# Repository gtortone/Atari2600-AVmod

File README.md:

# Atari2600-AVmod
Atari 2600 AV mod based on Longhorn A/V mod

## Bill of material

|Qty|Ref|Value|LibPart|Footprint|
|---|---|-----|-------|---------|
|1|C1|100uF|Device:C_Polarized|Capacitor_THT:CP_Radial_D5.0mm_P2.00mm|
|1|C2|1uF|Device:C_Polarized|Capacitor_THT:CP_Radial_D4.0mm_P2.00mm|
|1|C3|10uF|Device:C|Capacitor_THT:C_Disc_D4.7mm_W2.5mm_P5.00mm|
|2|C4, C5|.1uF|Device:C|Capacitor_THT:C_Disc_D4.7mm_W2.5mm_P5.00mm|
|1|D1|1N914|Diode:1N914|Diode_THT:D_DO-35_SOD27_P7.62mm_Horizontal|
|1|Q1|2N3904|Transistor_BJT:2N3904|Package_TO_SOT_THT:TO-92_Inline|
|1|R1|1k|Device:R|Resistor_THT:R_Axial_DIN0207_L6.3mm_D2.5mm_P10.16mm_Horizontal|
|1|R2|1.8k|Device:R|Resistor_THT:R_Axial_DIN0207_L6.3mm_D2.5mm_P10.16mm_Horizontal|
|1|R3|1.5k|Device:R|Resistor_THT:R_Axial_DIN0207_L6.3mm_D2.5mm_P10.16mm_Horizontal|
|1|R4|18k|Device:R|Resistor_THT:R_Axial_DIN0207_L6.3mm_D2.5mm_P10.16mm_Horizontal|
|1|R5|9.1k|Device:R|Resistor_THT:R_Axial_DIN0207_L6.3mm_D2.5mm_P10.16mm_Horizontal|
|1|R6|36k|Device:R|Resistor_THT:R_Axial_DIN0207_L6.3mm_D2.5mm_P10.16mm_Horizontal|
|1|R7|1.6k|Device:R|Resistor_THT:R_Axial_DIN0207_L6.3mm_D2.5mm_P10.16mm_Horizontal|
|1|R8|2k|Device:R|Resistor_THT:R_Axial_DIN0207_L6.3mm_D2.5mm_P10.16mm_Horizontal|
|1|R9|10|Device:R|Resistor_THT:R_Axial_DIN0207_L6.3mm_D2.5mm_P10.16mm_Horizontal||
|10|R10, R11, R12, R13, R14, R15, R16, R17, R18, R19|75|Device:R|Resistor_THT:R_Axial_DIN0207_L6.3mm_D2.5mm_P10.16mm_Horizontal|
|1|U1|CD74HC4050|4xxx:4050|Package_DIP:DIP-16_W7.62mm|
|1|U2|FMS6410|Video_filter:FMS6410|Package_SO:SOIC-8_3.9x4.9mm_P1.27mm|

## Schematic and PCB

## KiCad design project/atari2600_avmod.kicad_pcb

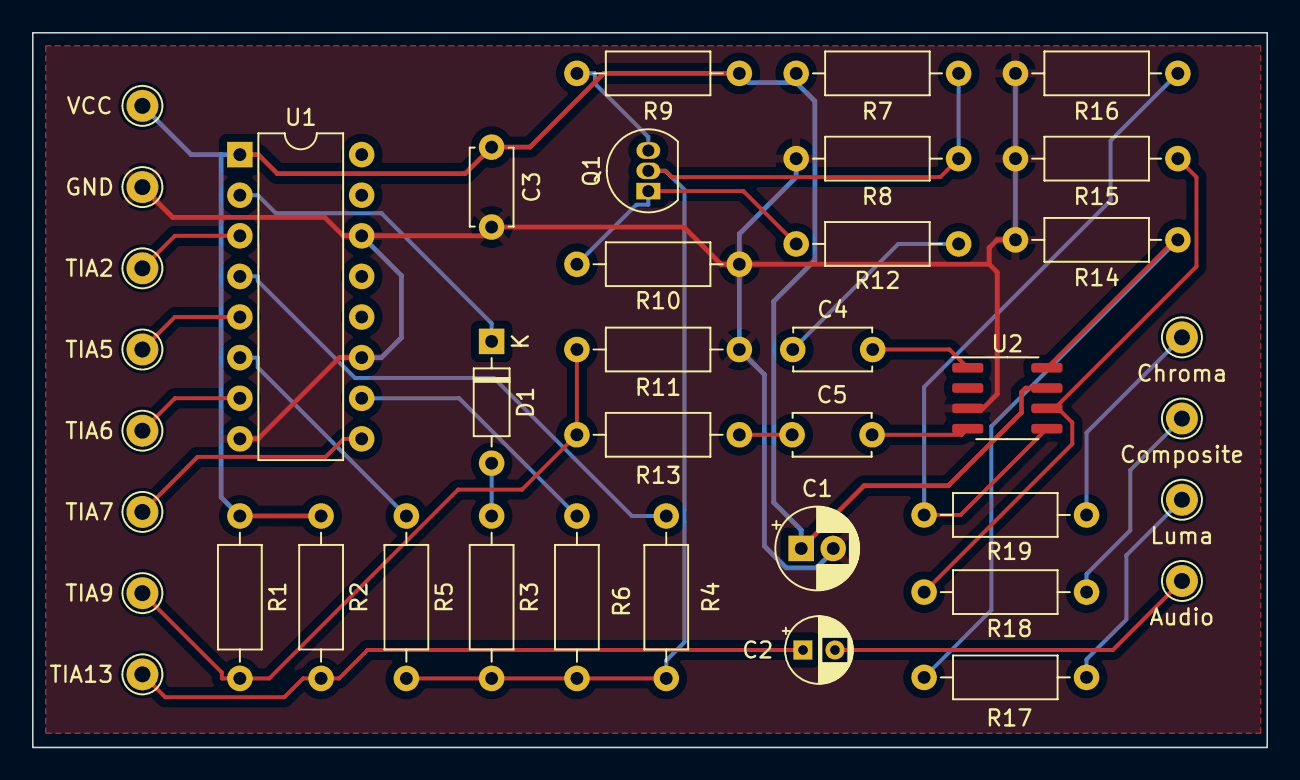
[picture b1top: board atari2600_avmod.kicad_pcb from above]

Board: 2 copper layers, 77.2 x 44.7 mm, 40 parts (0 on the bottom side), 27 nets.

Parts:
Audio: Pin_D1.0mm_L10.0mm
C1: 100uF; CP_Radial_D5.0mm_P2.00mm
C2: 1uF; CP_Radial_D4.0mm_P2.00mm
C3: 10uF; C_Disc_D4.7mm_W2.5mm_P5.00mm
C4, C5: .1uF; C_Disc_D4.7mm_W2.5mm_P5.00mm
Chroma: Pin_D1.0mm_L10.0mm
Composite: Pin_D1.0mm_L10.0mm
D1: 1N914; D_DO-35_SOD27_P7.62mm_Horizontal
GND: Pin_D1.0mm_L10.0mm
Luma: Pin_D1.0mm_L10.0mm
Q1: 2N3904; TO-92_Inline
R1: 1k; R_Axial_DIN0207_L6.3mm_D2.5mm_P10.16mm_Horizontal
R2: 1.8k; R_Axial_DIN0207_L6.3mm_D2.5mm_P10.16mm_Horizontal
R3: 1.5k; R_Axial_DIN0207_L6.3mm_D2.5mm_P10.16mm_Horizontal
R4: 18k; R_Axial_DIN0207_L6.3mm_D2.5mm_P10.16mm_Horizontal
R5: 9.1k; R_Axial_DIN0207_L6.3mm_D2.5mm_P10.16mm_Horizontal
R6: 36k; R_Axial_DIN0207_L6.3mm_D2.5mm_P10.16mm_Horizontal
R7: 1.6k; R_Axial_DIN0207_L6.3mm_D2.5mm_P10.16mm_Horizontal
R8: 2k; R_Axial_DIN0207_L6.3mm_D2.5mm_P10.16mm_Horizontal
R9: 10; R_Axial_DIN0207_L6.3mm_D2.5mm_P10.16mm_Horizontal
R10, R11, R12, R13, R14, R15, R16, R17, R18, R19: 75; R_Axial_DIN0207_L6.3mm_D2.5mm_P10.16mm_Horizontal
TIA2, TIA5, TIA6, TIA7, TIA9, TIA13: Pin_D1.0mm_L10.0mm
U1: 4050; DIP-16_W7.62mm
U2: SOIC-8_3.9x4.9mm_P1.27mm
VCC: Pin_D1.0mm_L10.0mm

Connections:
+5V: C1.1, C3.1, R1.1, R2.1, R7.2, R9.1, U1.1 (VCC), U2.7 (VCC), VCC.1
GND: C1.2, C3.2, GND.1, R8.2, R10.2, R11.1, R14.2, R15.2, R16.2, U1.8 (VSS), U1.11, U1.14, U2.3 (GND)
unnamed: Audio.1, C2.2
unnamed: C2.1, R2.2, TIA13.1
unnamed: C4.1, R12.2
unnamed: C5.1, R13.2
unnamed: Chroma.1, R19.2
unnamed: Composite.1, R18.2
unnamed: D1.2 (A), R3.1
unnamed: D1.1 (K), U1.2
unnamed: Luma.1, R17.2
unnamed: Q1.2 (B), R3.2, R4.2, R5.2, R6.2, R7.1, R8.1
unnamed: Q1.3 (C), R9.2
unnamed: Q1.1 (E), R10.1, R12.1
unnamed: R1.2, R11.2, R13.1, TIA9.1
unnamed: R4.1, U1.4
unnamed: R5.1, U1.6
unnamed: R6.1, U1.10
unnamed: TIA2.1, U1.3
unnamed: TIA5.1, U1.5
unnamed: TIA6.1, U1.7
unnamed: TIA7.1, U1.9
unnamed: C5.2, U2.4 (CIN)
unnamed: R16.1, R19.1, U2.5 (COUT)
unnamed: R15.1, R18.1, U2.6 (CVOUT)
unnamed: C4.2, U2.1 (YIN)
unnamed: R14.1, R17.1, U2.8 (YOUT)

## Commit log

2023-11-22 initial release
